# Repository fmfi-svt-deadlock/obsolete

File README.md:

# PROJECT MOVED

This repository is now hosted here: https://gitlab.com/project-deadlock/obsolete/obsolete-embedded-components

Cementery of obsolete components
================================

May they rest in peace.

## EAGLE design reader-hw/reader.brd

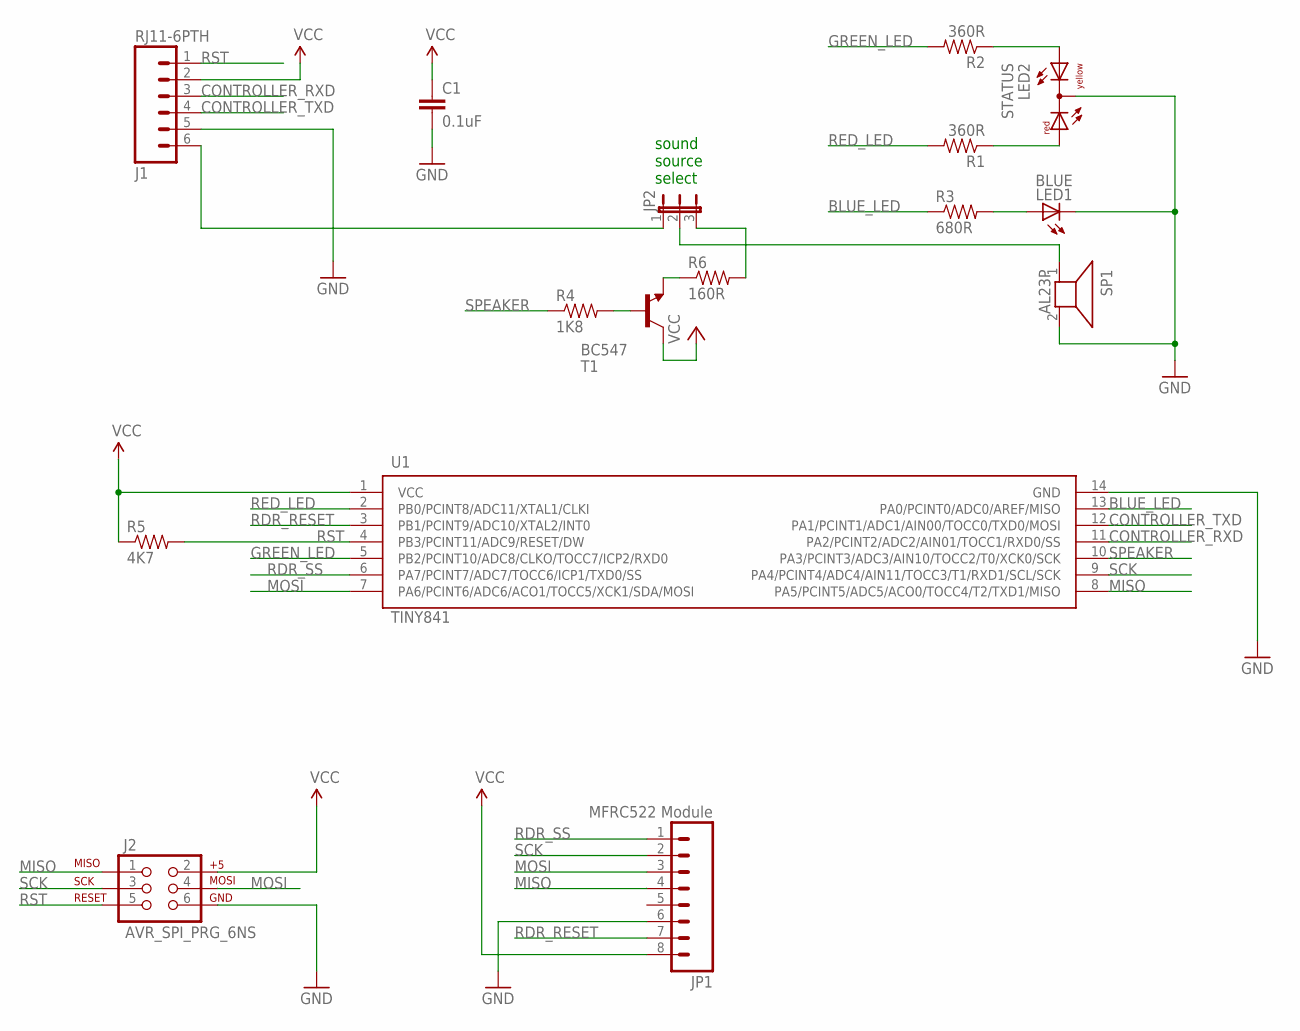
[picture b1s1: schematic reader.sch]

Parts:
C1: 0.1uF; CAP-PTH-SMALL-KIT
J1: RJ11-6PTH; RJ11-6
J2: AVR_SPI_PRG_6NS; 2X3-NS
JP1: MFRC522 Module; 1X08
JP2: JP2E; JP2
LED1: BLUE; LED3MM
LED2: STATUS; DUOLED-C-5MM
R1, R2: 360R; 0805
R3: 680R; 0805
R4: 1K8; 0805
R5: 4K7; 0805
R6: 160R; 0805
SP1: AL23P
T1: BC547; TO92
U1: TINY841; SO14

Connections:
BLUE_LED: R3.1, U1.13 (PA0/PCINT0/ADC0/AREF/MISO)
CONTROLLER_RXD: J1.3, U1.11 (PA2/PCINT2/ADC2/AIN01/TOCC1/RXD0/SS)
CONTROLLER_TXD: J1.4, U1.12 (PA1/PCINT1/ADC1/AIN00/TOCC0/TXD0/MOSI)
EXT_SPEAKER: J1.6, JP2.1
GND: C1.2, J1.5, J2.6, JP1.6, LED1.K (C), LED2.C, SP1.2, U1.14 (GND)
GREEN_LED: R2.2, U1.5 (PB2/PCINT10/ADC8/CLKO/TOCC7/ICP2/RXD0)
MISO: J2.1, JP1.4, U1.8 (PA5/PCINT5/ADC5/ACO0/TOCC4/T2/TXD1/MISO)
MOSI: J2.4, JP1.3, U1.7 (PA6/PCINT6/ADC6/ACO1/TOCC5/XCK1/SDA/MOSI)
unnamed: JP2.2, SP1.1
unnamed: LED2.AR, R1.1
unnamed: LED2.AX (AY), R2.1
unnamed: R4.2, T1.2 (B)
unnamed: R6.1, T1.1 (E)
unnamed: LED1.A, R3.2
unnamed: JP2.3, R6.2
RDR_RESET: JP1.7, U1.3 (PB1/PCINT9/ADC10/XTAL2/INT0)
RDR_SS: JP1.1, U1.6 (PA7/PCINT7/ADC7/TOCC6/ICP1/TXD0/SS)
RED_LED: R1.2, U1.2 (PB0/PCINT8/ADC11/XTAL1/CLKI)
RST: J1.1, J2.5, R5.2, U1.4 (PB3/PCINT11/ADC9/RESET/DW)
SCK: J2.3, JP1.2, U1.9 (PA4/PCINT4/ADC4/AIN11/TOCC3/T1/RXD1/SCL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)
SPEAKER: R4.1, U1.10 (PA3/PCINT3/ADC3/AIN10/TOCC2/T0/XCK0/SCK)
VCC: C1.1, J1.2, J2.2, JP1.8, R5.1, T1.3 (C), U1.1 (VCC)

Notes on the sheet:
sound source select

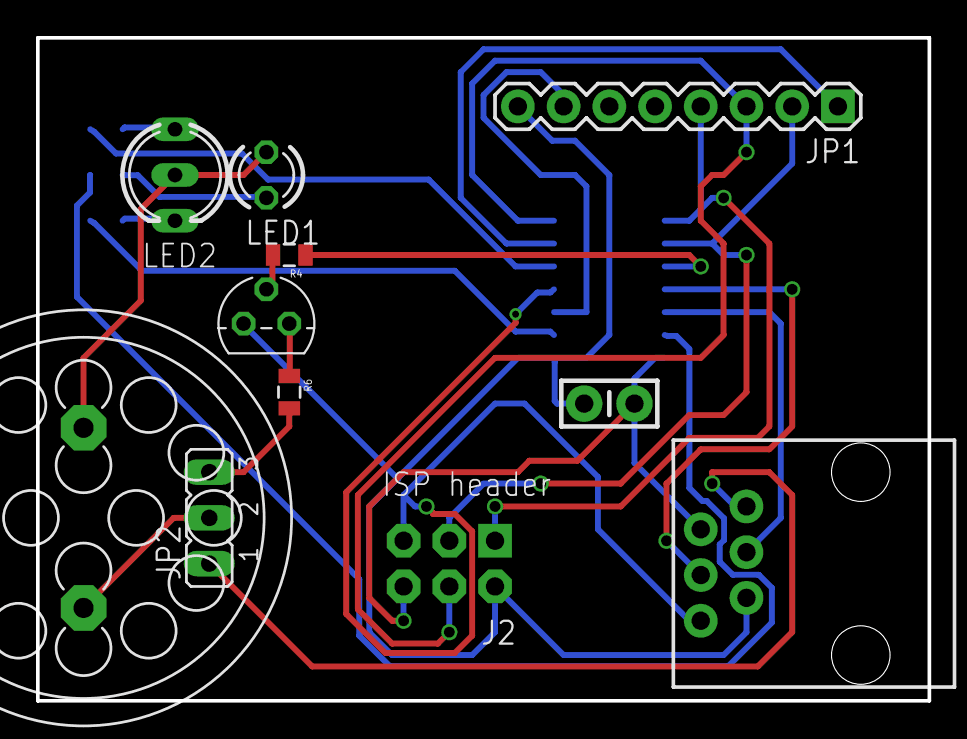
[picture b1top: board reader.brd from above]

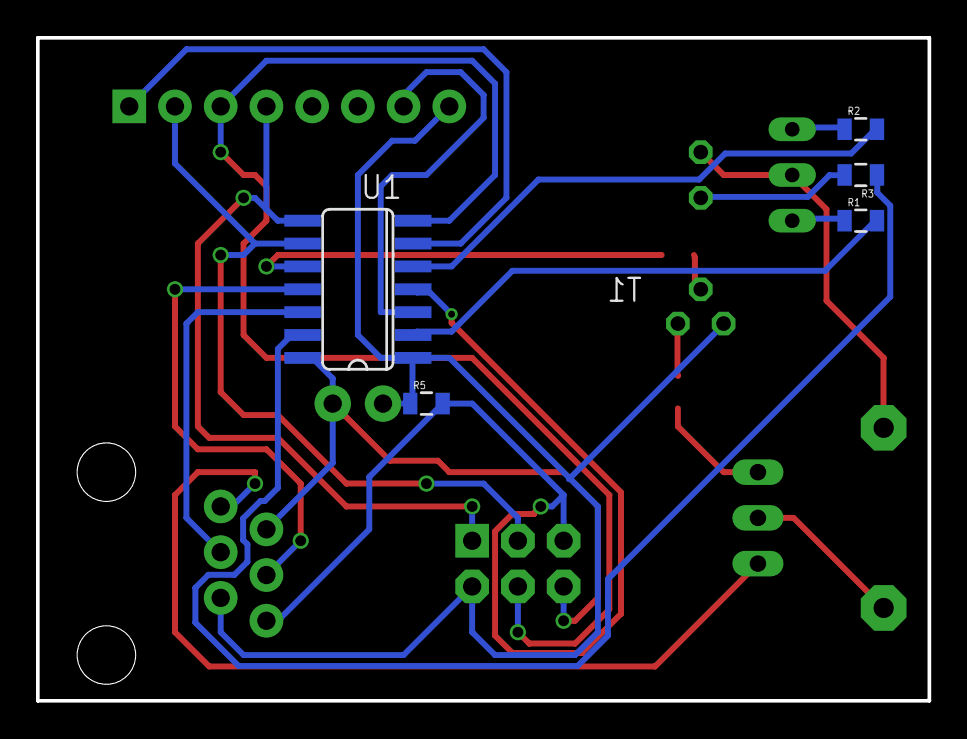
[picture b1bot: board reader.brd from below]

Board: 2 copper layers, 49.5 x 36.8 mm, 16 parts (5 on the bottom side), 22 nets.

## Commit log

2015-01-31 Add LICENSE and README
2015-02-01 Initial commit (create branch)
2015-02-01 Add .gitignore
2015-02-01 Add LICENSE
2015-02-01 Add Makefile
2015-02-01 Add README
2015-02-01 Add note about the avrdude config
2015-02-01 Add missing endlines at the end of files
2015-02-01 Remove -funsigned-bitfields from the Makefile
    So that nobody would be tempted to use them.
2015-02-03 Add hardware description header
2015-02-04 Fix indentation in board.h
2015-02-04 Add HAL stub
2015-02-04 Ignore EEPROM (.eep) compiled files
2015-02-04 Make clean recipe delete also generated .hex (flash image) and .eep (eeprom image)
2015-02-05 Add hal_ prefix to the HAL functions
2015-02-05 Add header with macros for bit manipulation
2015-02-05 Implement HAL for LEDs
2015-02-06 Add HW revision note to the Speaker HAL
2015-02-06 Add recipe for programming fuse bits, change frequency to 8MHz
2015-02-06 Change the HAL configuration mechanism
2015-02-07 Implement SPI HAL
2015-02-07 Fix swapped definitions for RED and GREEN leds
2015-02-08 Change HAL configuration to match the RevB board
2015-02-08 [WIP] Implement beeping HAL (no callbacks, cannot be stopped yet)
2015-02-09 Add speaker HAL
2015-02-10 Implement usart hal
2015-02-11 Code cleanup
2015-02-11 Add more comments to the HAL
2015-02-11 Update Readme - note about the fuses
2015-02-11 Fix newlines, blank spaces and comments
2015-02-11 Fix indentation
2015-02-13 [WIP] Add comm module and protocol headers
2015-02-14 Change HAL USART API
2015-02-14 Implement packet reception and transmission
2015-02-14 [WIP] Implement processing of Status, LED and RFID Tx packets
2015-02-15 [HAL] Add function for stopping current beeping
2015-02-15 [WIP] Implement handling of a Beep packet
2015-02-15 Reflect recent protocol changes
    Limit the packet payload size to 128 bytes, remove references to the
    Degraded mode, change ACK packet (remove RFID Status byte)
2015-02-15 Implement last packet retransmission
2015-02-15 Remove return value from HAL initialization. It wasn't being used anywhere
2015-02-15 [HAL] Implement low-precision timer
2015-02-15 Implement reception timeout
2015-02-16 Refactor constant names to be uppercase
2015-02-16 Do not ambiguously initialize variables on two places
2015-02-16 Add ommited comments
2015-02-18 [HAL] Add begin_transaction and end_transaction to SPI HAL
2015-02-26 Clean all connections from the board
2015-02-26 Add a switch transistor to drive the speaker
2015-02-26 Swap SPEAKER and BLUE_LED, reorganize components
2015-02-26 [WIP] Manually route few connectors on the board
2015-02-26 Reroute the board
2015-03-18 Move everything to reader-hw folder
2015-03-18 Move everything to reader-sw folder

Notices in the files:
parts and their libraries:
SparkFun-Capacitors: Licensing: Creative Commons ShareAlike 4.0 International - https://creativecommons.org/licenses/by-sa/4.0
